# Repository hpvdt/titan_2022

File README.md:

# TITAN Video System

This is the code and hardware that is used to drive the electronics aboard TITAN for the "drive-by-video" system used for the World Human Powered Speed Challenge 2022.

>[!NOTE]
> This repository is meant to a snapshot of the system used for the 2022 system for TITAN, and was archived in November 2023. It was only unarchived to add a written summary of [operating instructions](./OPERATION.md) should it need to be reused. However no changes to the system itself have happened since 2023.
>
> For information on the the newest system in 2026 please go to that one's [separate repository](https://github.com/savob/titan_2026).

This code is spread across two types of devices, an STM32 microcontroller (STM32F103C8 is used in current models) and Raspberry Pis (RPi) Model 3B+'s. Each rider has an RPi for a total of two units, while there is only one STM32 for the vehicle. The STM32 is primarily responsible for collecting vehicle data and passing it to the RPis when requested. The RPis are responsible for displaying the video feed from the RPi Cameras used (hence why each rider needs their own) with an overlay of data collected inside the vehicle. This overlay is tailored to each rider.

There is an additional redundant video system for the front rider based on analog video to minimize potential failure points. This system was entirely off the shelf except for the power regulator, and was entirely disconnected from the remainder of TITAN's electronics to prevent any failure cascade affecting it.

## Folders

The repository is split into folders based on function.

Folder | Purpose
------ | -------
`Hardware` | Hardware files for our circuit boards
`Microcontroller Code` | STM32 Code
`vision` | RPi video code in C

## Hardware

The hardware for TITAN was all designed in [KiCad](https://www.kicad.org/) there are all three boards designed for TITAN with a `readme.md` explaining their purposes. Below is a block diagram of the TITAN system.

## Microcontroller Code

This is the collection of code prepared for the microcontroller on TITAN. It contains the unit tests we prepared when developing and testing different features that would eventually be integrated into TITAN, a local copy of the GPS library we use, and the overall program for TITAN.

TITAN was initially coded entirely within the Arduino IDE, however we migrated to using VS Code and PlatformIO to help make development easier and also make use of debugging features absent in the original Arduino IDE.

## Raspberry Pi Code

These are responsible for putting video on the displays for the riders to see, overlaid with information about TITAN. One of the RPi's has an ANT+ USB module used to collect data from the heart rate monitor and power pedals each rider has and feed it to the STM32 to pass onto the other RPi.

**The program for running the video feed is run as a separate process to the overlay**, this way if there is a hardware malfunction for the overlay (e.g. the STM32 freezes) then the video feed is uninterrupted for the riders.

The code for vision is split between Python and C. The video related code is written in Python, as well as a few other scripts for operation. The overlay code is written in C using the chipset driver library unique to the RPi 3 hardware to draw the overlay so it cannot be used on RPi models other then the 3B or 3B+ (and must be compiled specifically for each model).

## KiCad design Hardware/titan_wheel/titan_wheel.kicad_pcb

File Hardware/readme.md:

# TITAN Hardware

These folders contain the files related to hardware designed to operate TITAN. They were all designed using KiCad 6.0.2.

## Overview

The TITAN hardware is designed to primarily be a HAT (**HA**rdware on **T**op) for the Raspberry Pi 3B+s we use for video. This form factor was chosen to reduce the overall footprint of the system compared to the original 2019 system which used a ribbon cable between the RPi and boards. This also reduces the chance of incorrect connections since the HAT can only be seated one way. At the heart of the HAT, there is an STM32F103C microcontroller which communicates with the RPis and various sensors around TITAN via the various connections present.

These HATs perform 4 main functions:
1. Regulate power for their RPi and monitor from the battery. (Reverse polarity and undervoltage protection built in).
2. Facilitate communication between RPis via an STM32 microcontroller
3. Collect data from TITAN using the STM32 microcontroller
4. Handle telemetry with the chase vechicle

**Functions 2 to 4 are only performed on the "main" (front) unit, where the STM32 is.** The secondary (rear) does not have the STM32 mounted and just uses the power system and a header to connect to the main board for data.

## The Boards

There are three boards/folders/projects present in the folder, representing two revisions of the hardware. 

### TITAN Redux (2020)

Following feedback from the 2019 WHPSC and experience in developing [Blueshift](https://github.com/hpvdt/blueshift), an initial revision of TITAN was made in the fall of 2020, dubbed `titan_redux`. This was the main revision from the 2019 system, moving to the HAT form factor which worked on Blueshift as well as moving to embed the microconroller directly on the board (as opposed to seating a "Blue Pill" development board) and using SMT to reduce the overall size.

This was largely successful and allowed most of the code that went into TITAN in 2022 to be properly tested. There were only two notable issues with it:
1. The RX and TX lines for the GPS were not properly crossed over to the STM32.
2. The 5V regulator was removed for undocumented reasons, likely due to a failure.

### TITAN 2022

The more straightforwardly named `titan_2022` is a revision of the Redux board. It addresses the issues it had as well as adding support for new features while maintaining the same RPi HAT form. A brief of the changes:

- Fixed UART lines
- Rearranged board for improved button access
- Rearranged sensors to simplify routing
- Changed to a different 5V regulator (largely due to supply issues)
- Moved DHT sensor and encoder comparator off-board
- Added headers for monitoring CO2 and brake temperature

### TITAN Wheel (2022)

As part of the revision process from redux to the 2022 system a daughter board to collect wheel data was prepared called `titan_wheel`. This board houses the brake temperature sensor as well as the optical encoder and its conditioning circuitry. It was designed to fit within the wheel structure close to the brake disk.

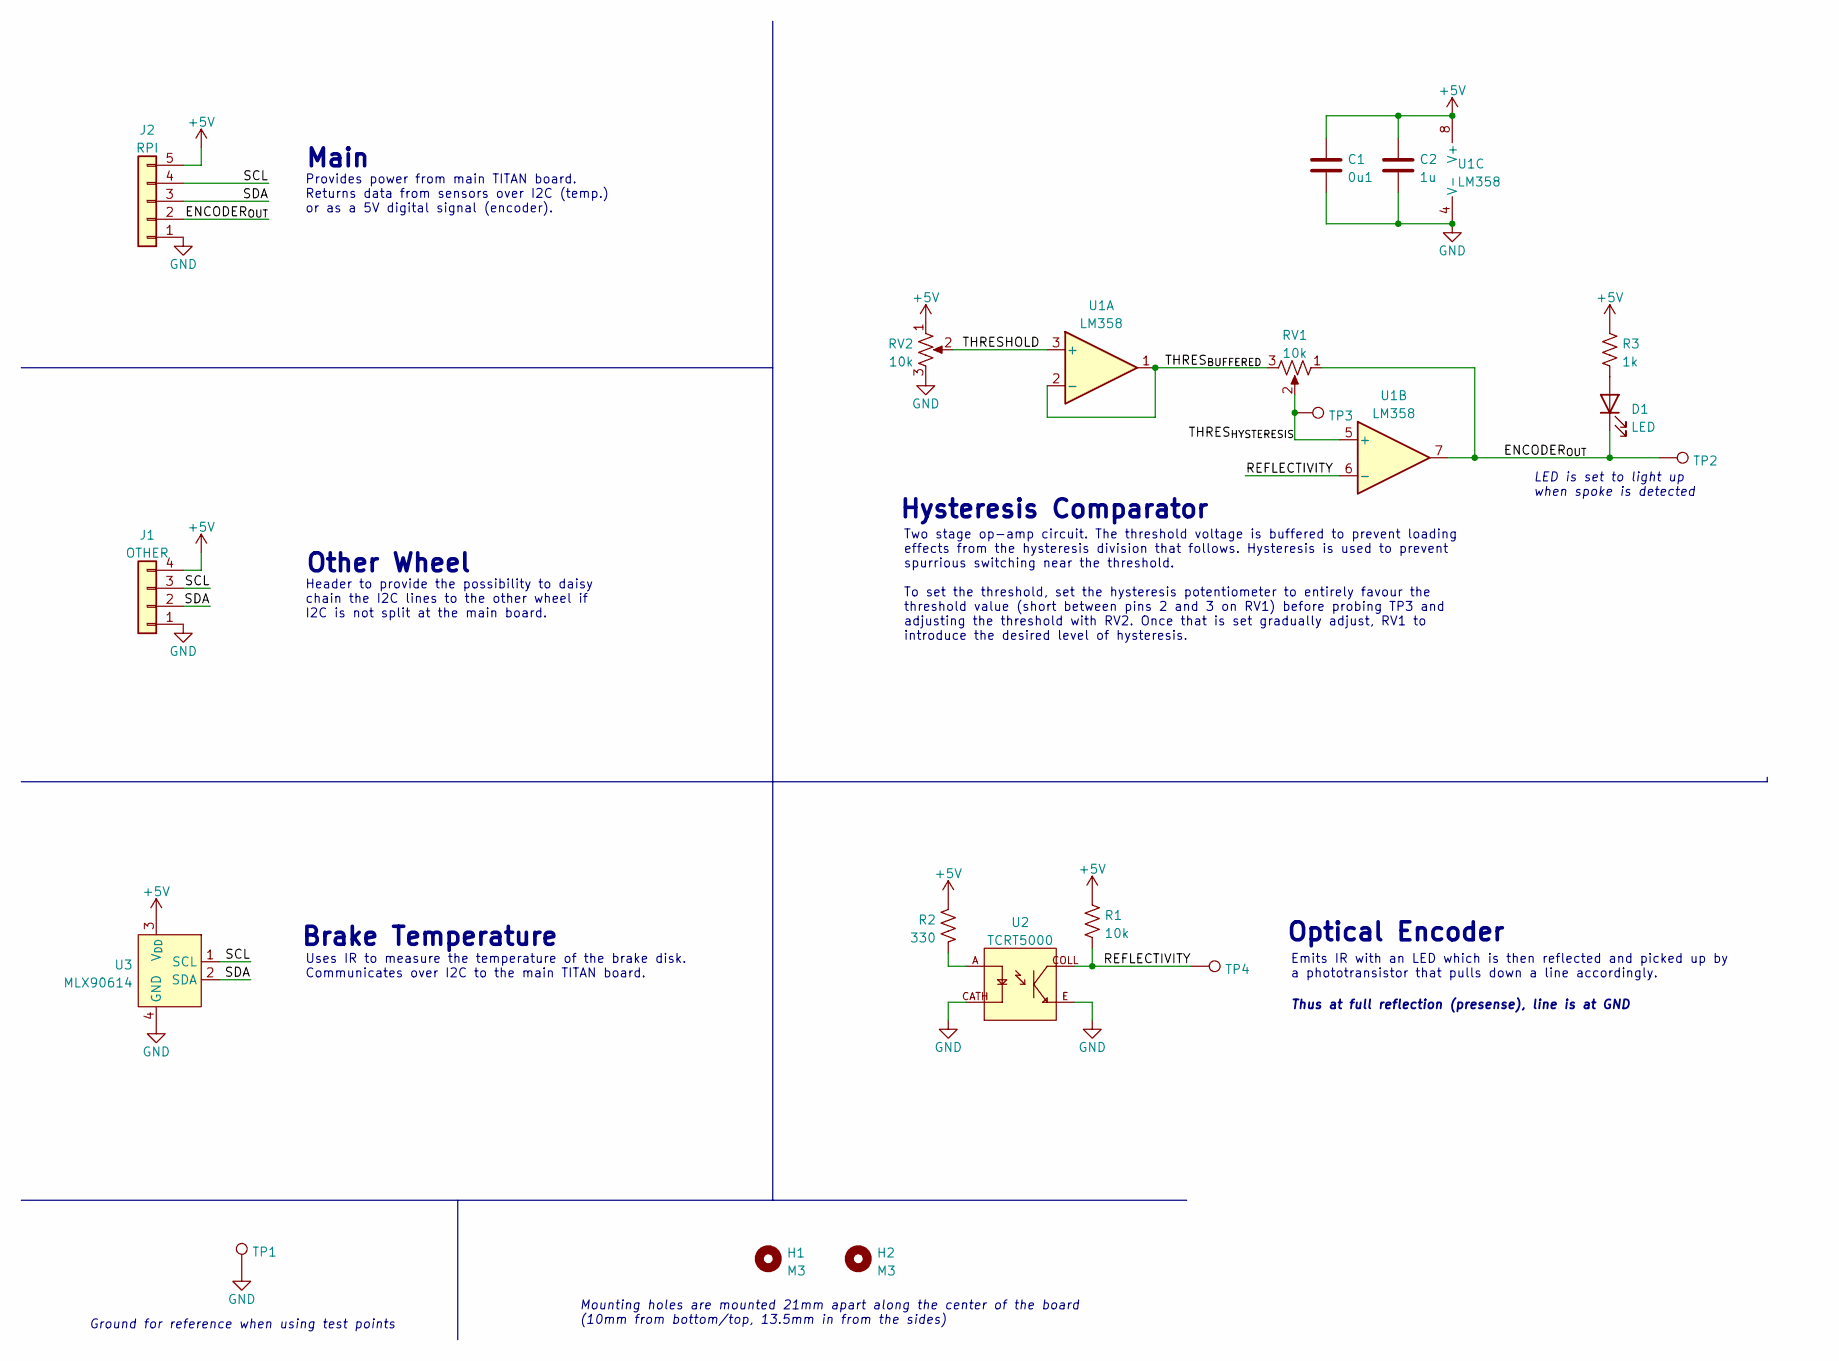
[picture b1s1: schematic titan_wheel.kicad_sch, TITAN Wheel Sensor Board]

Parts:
C1: 0u1; C_0603_1608Metric
C2: 1u; C_0603_1608Metric
D1: LED; LED_0805_2012Metric
H1, H2: M3; MountingHole_3.2mm_M3
J1: OTHER; PinHeader_1x04_P2.54mm_Vertical
J2: RPI; PinHeader_1x05_P2.54mm_Vertical
R1: 10k; R_0603_1608Metric
R2: 330; R_0603_1608Metric
R3: 1k; R_0603_1608Metric
RV1, RV2: 10k; Potentiometer_Vishay_T73YP_Vertical
TP1, TP2, TP3, TP4: TestPoint; TestPoint_Bridge_Pitch2.54mm_Drill1.0mm
U1: LM358; SOIC-8_3.9x4.9mm_P1.27mm
U2: TCRT5000; OPTO_TCRT5000; PARTREV 1.7
U3: MLX90614; TO-39-4_Window

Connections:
+5V: C1.1, C2.1, J1.4, J2.5, R1.1, R2.2, R3.1, RV2.1, U1.8 (V+), U3.3 (V_{DD})
/ENCODER_{OUT}: D1.1 (K), J2.2, RV1.1, TP2.1, U1.7
/REFLECTIVITY: R1.2, TP4.1, U1.6 (-), U2.COLL
/SCL: J1.3, J2.4, U3.1 (SCL)
/SDA: J1.2, J2.3, U3.2 (SDA)
/THRESHOLD: RV2.2, U1.3 (+)
/THRES_{BUFFERED}: RV1.3, U1.1, U1.2 (-)
/THRES_{HYSTERESIS}: RV1.2, TP3.1, U1.5 (+)
GND: C1.2, C2.2, J1.1, J2.1, RV2.3, TP1.1, U1.4 (V-), U2.CATH, U2.E, U3.4 (GND)
unnamed: D1.2 (A), R3.2
unnamed: R2.1, U2.A

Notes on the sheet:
Mounting holes are mounted 21mm apart along the center of the board (10mm from bottom/top, 13.5mm in from the sides)
Hysteresis Comparator
Provides power from main TITAN board. Returns data from sensors over I2C (temp.) or as a 5V digital signal (encoder).
Emits IR with an LED which is then reflected and picked up by a phototransistor that pulls down a line accordingly.
Two stage op-amp circuit. The threshold voltage is buffered to prevent loading effects from the hysteresis division that follows. Hysteresis is used to prevent spurrious switching near the threshold. To set the threshold, set the hysteresis potentiometer to entirely favour the threshold value (shor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
Ground for reference when using test points
Optical Encoder
Main
Other Wheel
LED is set to light up when spoke is detected
Brake Temperature
Header to provide the possibility to daisy chain the I2C lines to the other wheel if I2C is not split at the main board.
Uses IR to measure the temperature of the brake disk. Communicates over I2C to the main TITAN board.
Thus at full reflection (presense), line is at GND

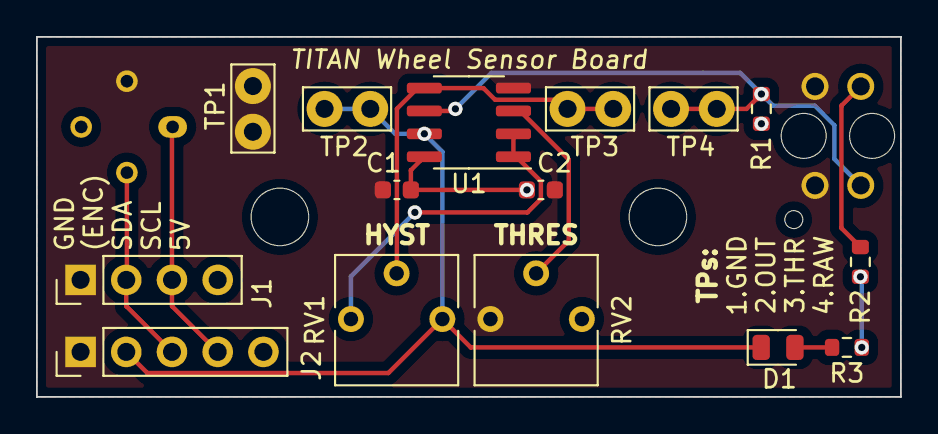
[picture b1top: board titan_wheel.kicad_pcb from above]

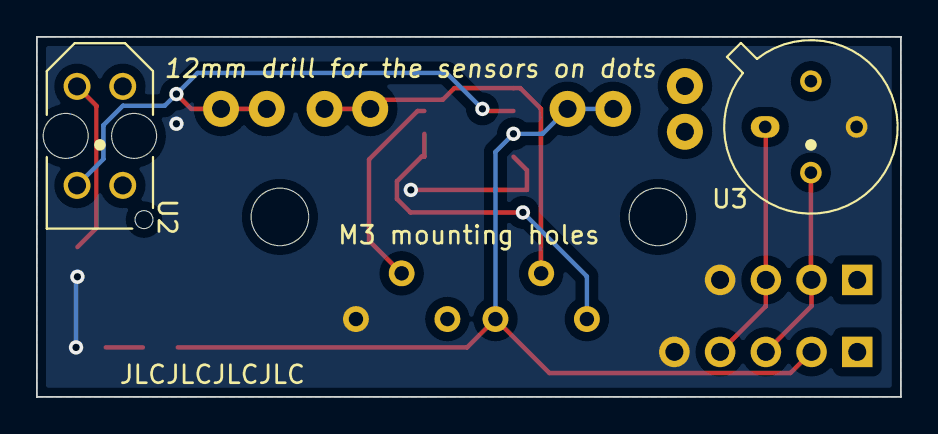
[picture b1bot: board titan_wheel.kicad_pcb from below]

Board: 2 copper layers, 48.0 x 20.0 mm, 19 parts (2 on the bottom side), 11 nets.

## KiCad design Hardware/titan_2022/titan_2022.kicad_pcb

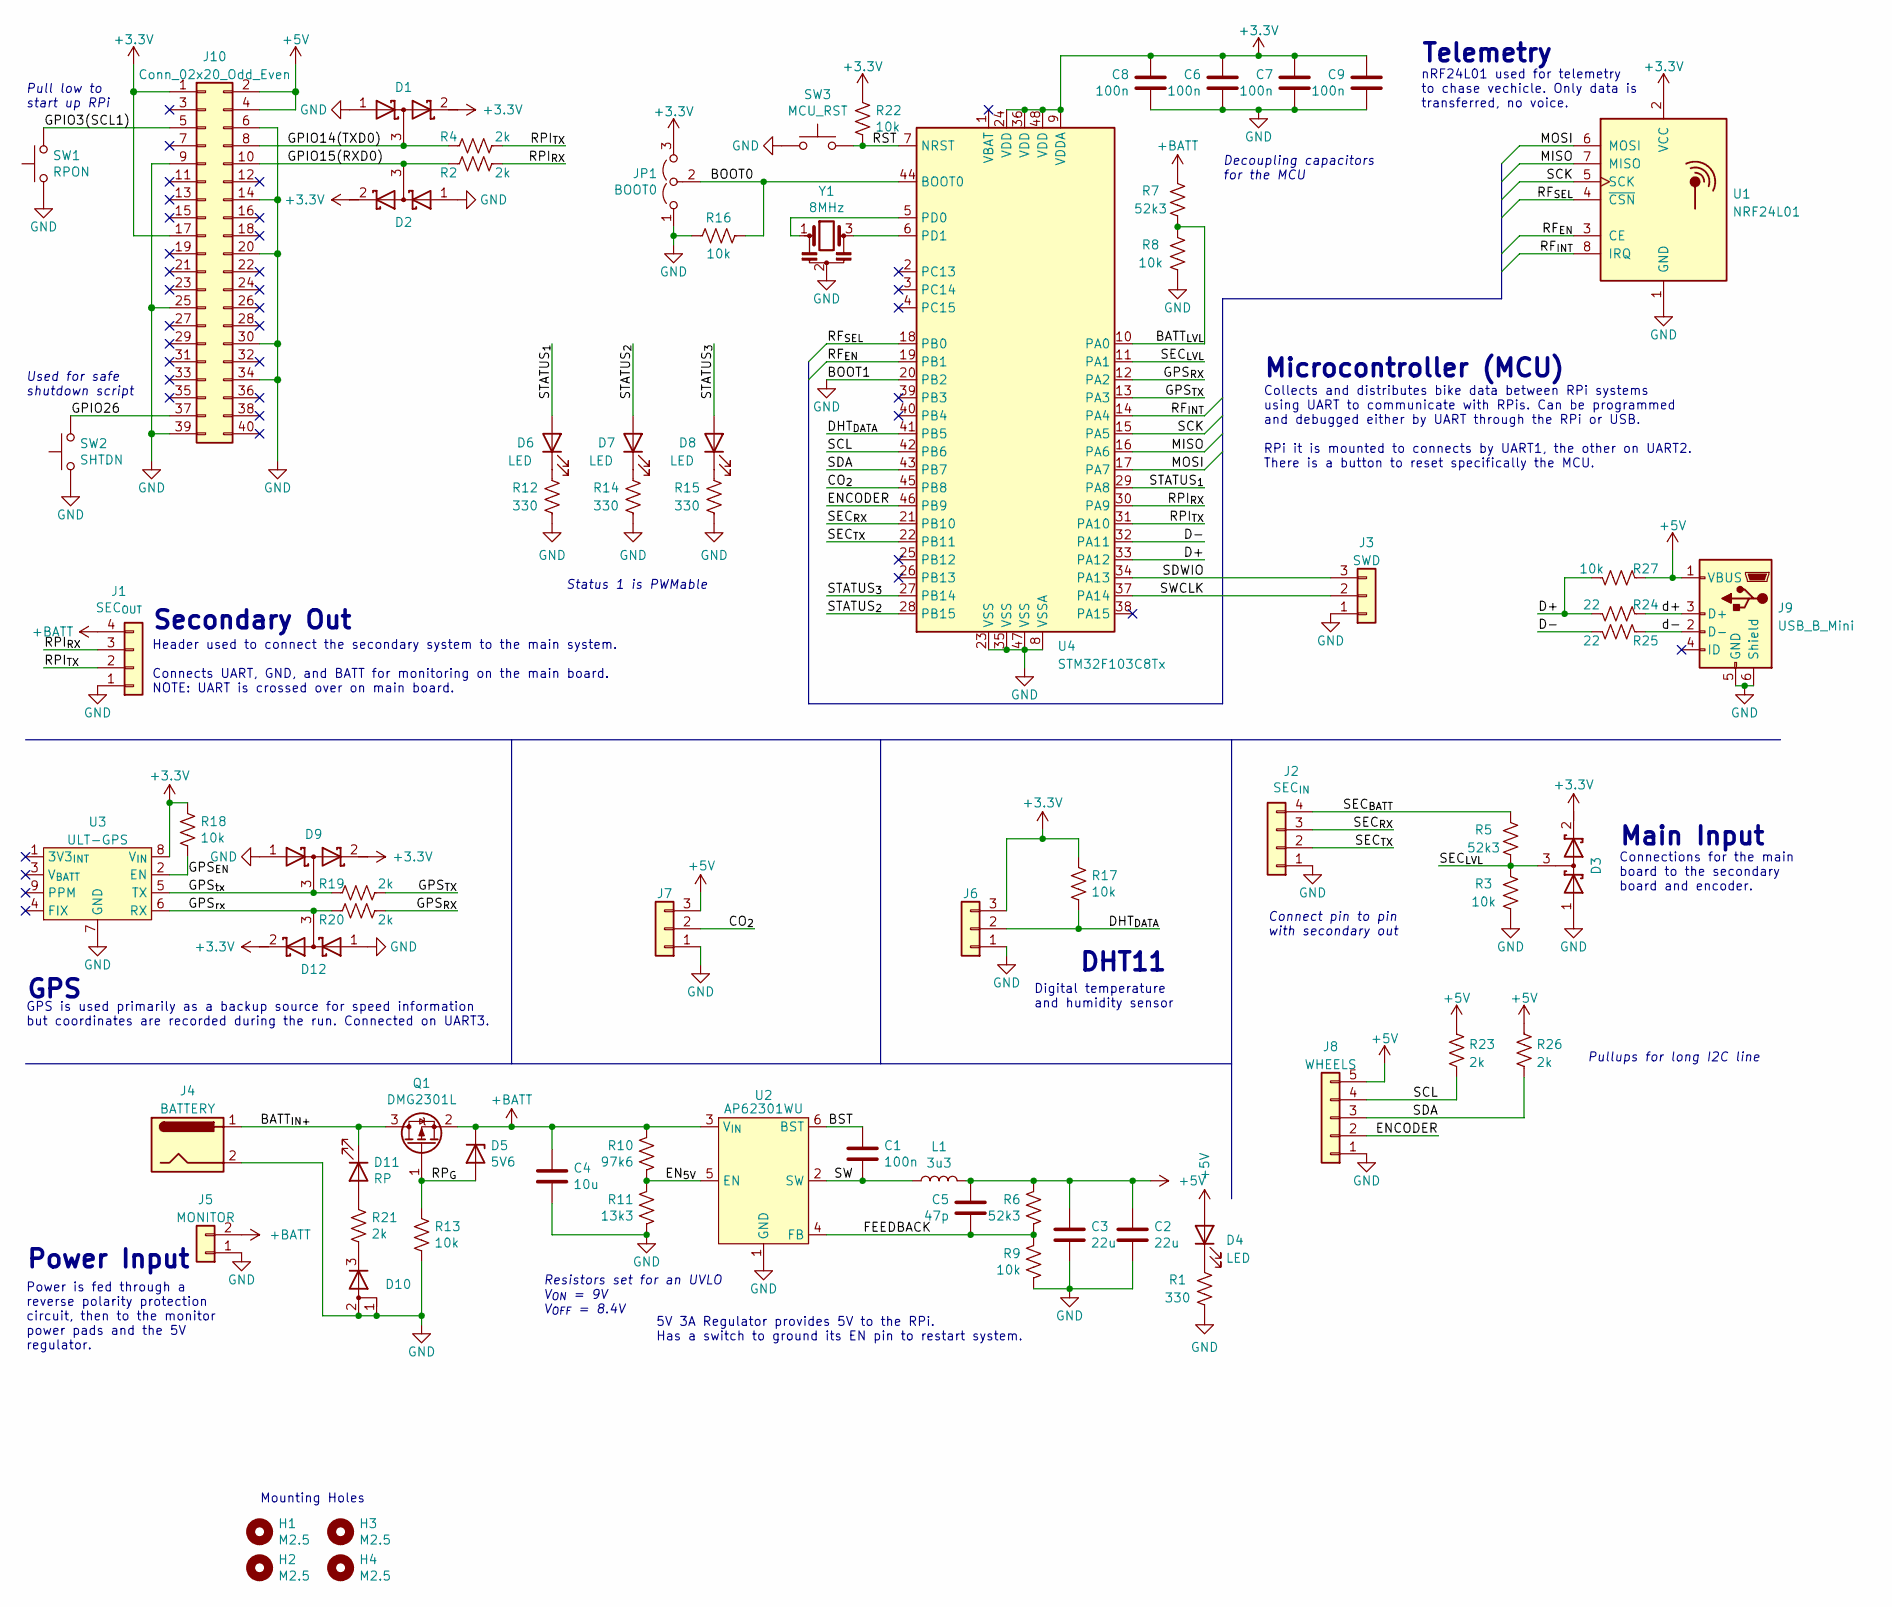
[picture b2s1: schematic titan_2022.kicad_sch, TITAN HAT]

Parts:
C1, C6, C7, C8, C9: 100n; C_0603_1608Metric
C2, C3: 22u; C_0805_2012Metric
C4: 10u; C_0603_1608Metric
C5: 47p; C_0603_1608Metric
D1, D2, D3, D9, D12: TBAT54S; SOT-23
D4, D6, D7, D8: LED; LED_0805_2012Metric
D5: 5V6; D_SOD-323
D10: BAV70; SOT-23
D11: RP; D_0805_2012Metric
H1, H2, H3, H4: M2.5; MountingHole_2.7mm_M2.5
J1: SEC_{OUT}; Molex_KK-254_AE-6410-04A_1x04_P2.54mm_Vertical
J2: SEC_{IN}; Molex_KK-254_AE-6410-04A_1x04_P2.54mm_Vertical
J3: SWD; PinHeader_1x03_P2.54mm_Vertical
J4: BATTERY; BarrelJack_Wuerth_6941xx301002
J5: MONITOR; SolderWire-1.5sqmm_1x02_P6mm_D1.7mm_OD3mm
J6: DHT; PinHeader_1x03_P2.54mm_Vertical
J7: CO_{2}; PinHeader_1x03_P2.54mm_Vertical
J8: WHEELS; PinHeader_1x05_P2.54mm_Vertical
J9: USB_B_Mini; TE_2172034-1
J10: Conn_02x20_Odd_Even; PinSocket_2x20_P2.54mm_Vertical
JP1: BOOT0; PinHeader_1x03_P2.54mm_Vertical
L1: 3u3; L_Taiyo-Yuden_NR-50xx
Q1: DMG2301L; SOT-23
R1, R12, R14, R15: 330; R_0603_1608Metric
R2, R4, R19, R20, R21, R23, R26: 2k; R_0603_1608Metric
R3, R8, R9, R13, R16, R17, R18, R22, R27: 10k; R_0603_1608Metric
R5, R6, R7: 52k3; R_0603_1608Metric
R10: 97k6; R_0603_1608Metric
R11: 13k3; R_0603_1608Metric
R24, R25: 22; R_0603_1608Metric
SW1: RPON; SW_PUSH_6mm_H4.3mm
SW2: SHTDN; SW_PUSH_6mm_H4.3mm
SW3: MCU_RST; SW_PUSH_6mm_H4.3mm
U1: NRF24L01; nRF24L01_Breakout
U2: AP62301WU; TSOT-23-6
U3: ULT-GPS
U4: STM32F103C8Tx; LQFP-48_7x7mm_P0.5mm
Y1: 8MHz; Resonator_SMD_Murata_CSTxExxV-3Pin_3.0x1.1mm

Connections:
+3V3: C6.2, C7.2, C8.2, C9.2, D1.2 (K), D2.2 (K), D3.2 (K), D9.2 (K), D12.2 (K), J6.3, J10.1, J10.17, JP1.3 (B), R17.2, R18.2, R22.2, U1.2 (VCC), U3.8 (V_{IN}), U4.9 (VDDA), U4.24 (VDD), U4.36 (VDD), U4.48 (VDD)
+5V: C2.1, C3.1, C5.2, D4.2 (A), J7.3, J8.5, J9.1 (VBUS), J10.2, J10.4, L1.2, R6.2, R23.1, R26.1, R27.2
+BATT: C4.2, D5.1 (K), J1.4, J5.2, Q1.2 (S), R7.2, R10.2, U2.3 (V_{IN})
/BATT_{IN+}: D11.1 (K), J4.1, Q1.3 (D)
/BATT_{LVL}: R7.1, R8.2, U4.10 (PA0)
/BOOT0: JP1.2 (C), R16.2, U4.44 (BOOT0)
/BST: C1.2, U2.6 (BST)
/CO_{2}: J7.2, U4.45 (PB8)
/D+: R24.1, R27.1, U4.33 (PA12)
/D-: R25.1, U4.32 (PA11)
/DHT_{DATA}: J6.2, R17.1, U4.41 (PB5)
/ENCODER: J8.2, U4.46 (PB9)
/EN_{5V}: R10.1, R11.2, U2.5 (EN)
/FEEDBACK: C5.1, R6.1, R9.2, U2.4 (FB)
/GPIO3(SCL1): J10.5, SW1.2
/GPIO14(TXD0): D1.3 (common), J10.8, R4.2
/GPIO15(RXD0): D2.3 (common), J10.10, R2.2
/GPIO26: J10.37, SW2.2
/GPS_{EN}: R18.1, U3.2 (EN)
/GPS_{RX}: R20.1, U4.12 (PA2)
/GPS_{TX}: R19.1, U4.13 (PA3)
/GPS_{rx}: D12.3 (common), R20.2, U3.6 (RX)
/GPS_{tx}: D9.3 (common), R19.2, U3.5 (TX)
/MISO: U1.7 (MISO), U4.16 (PA6)
/MOSI: U1.6 (MOSI), U4.17 (PA7)
/RF_{EN}: U1.3 (CE), U4.19 (PB1)
/RF_{INT}: U1.8 (IRQ), U4.14 (PA4)
/RF_{SEL}: U1.4 (~CSN), U4.18 (PB0)
/RPI_{RX}: J1.3, R2.1, U4.30 (PA9)
/RPI_{TX}: J1.2, R4.1, U4.31 (PA10)
/RP_{G}: D5.2 (A), Q1.1 (G), R13.2
/RST: R22.1, SW3.2, U4.7 (NRST)
/SCK: U1.5 (SCK), U4.15 (PA5)
/SCL: J8.4, R23.2, U4.42 (PB6)
/SDA: J8.3, R26.2, U4.43 (PB7)
/SDWIO: J3.3, U4.34 (PA13)
/SEC_{BATT}: J2.4, R5.2
/SEC_{LVL}: D3.3 (common), R3.2, R5.1, U4.11 (PA1)
/SEC_{RX}: J2.3, U4.21 (PB10)
/SEC_{TX}: J2.2, U4.22 (PB11)
/STATUS_{1}: D6.2 (A), U4.29 (PA8)
/STATUS_{2}: D7.2 (A), U4.28 (PB15)
/STATUS_{3}: D8.2 (A), U4.27 (PB14)
/SW: C1.1, L1.1, U2.2 (SW)
/SWCLK: J3.2, U4.37 (PA14)
/d+: J9.3 (D+), R24.2
/d-: J9.2 (D-), R25.2
GND: C2.2, C3.2, C4.1, C6.1, C7.1, C8.1, C9.1, D1.1 (A), D2.1 (A), D3.1 (A), D9.1 (A), D10.1 (A), D10.2 (A), D12.1 (A), J1.1, J2.1, J3.1, J4.2, J5.1, J6.1, J7.1, J8.1, J9.5 (GND), J9.6 (Shield), J10.6, J10.9, J10.14, J10.20, J10.25, J10.30, J10.34, J10.39, JP1.1 (A), R1.1, R3.1, R8.1, R9.1, R11.1, R12.1, R13.1, R14.1, R15.1, R16.1, SW1.1, SW2.1, SW3.1, U1.1 (GND), U2.1 (GND), U3.7 (GND), U4.8 (VSSA), U4.20 (PB2), U4.23 (VSS), U4.35 (VSS), U4.47 (VSS), Y1.2
unnamed: D4.1 (K), R1.2
unnamed: D6.1 (K), R12.2
unnamed: D7.1 (K), R14.2
unnamed: D8.1 (K), R15.2
unnamed: D10.3 (K), R21.1
unnamed: D11.2 (A), R21.2
unnamed: U4.5 (PD0), Y1.1
unnamed: U4.6 (PD1), Y1.3

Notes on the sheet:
Power is fed through a reverse polarity protection circuit, then to the monitor power pads and the 5V regulator.
Microcontroller (MCU)
Connections for the main board to the secondary board and encoder.
GPS
Connect pin to pin with secondary out
Status 1 is PWMable
nRF24L01 used for telemetry to chase vechicle. Only data is transferred, no voice.
Decoupling capacitors for the MCU
Power Input
Collects and distributes bike data between RPi systems using UART to communicate with RPis. Can be programmed and debugged either by UART through the RPi or USB. RPi it is mounted to connects by UART1, the other on UART2. There is a button to reset specifically the MCU.
Header used to connect the secondary system to the main system. Connects UART, GND, and BATT for monitoring on the main board. NOTE: UART is crossed over on main board.
Secondary Out
Mounting Holes
Pullups for long I2C line
Digital temperature and humidity sensor
GPS is used primarily as a backup source for speed information but coordinates are recorded during the run. Connected on UART3.
Pull low to start up RPi
Used for safe shutdown script
5V 3A Regulator provides 5V to the RPi. Has a switch to ground its EN pin to restart system.
DHT11
Resistors set for an UVLO V_{ON} = 9V V_{OFF} = 8.4V
Main Input
Telemetry

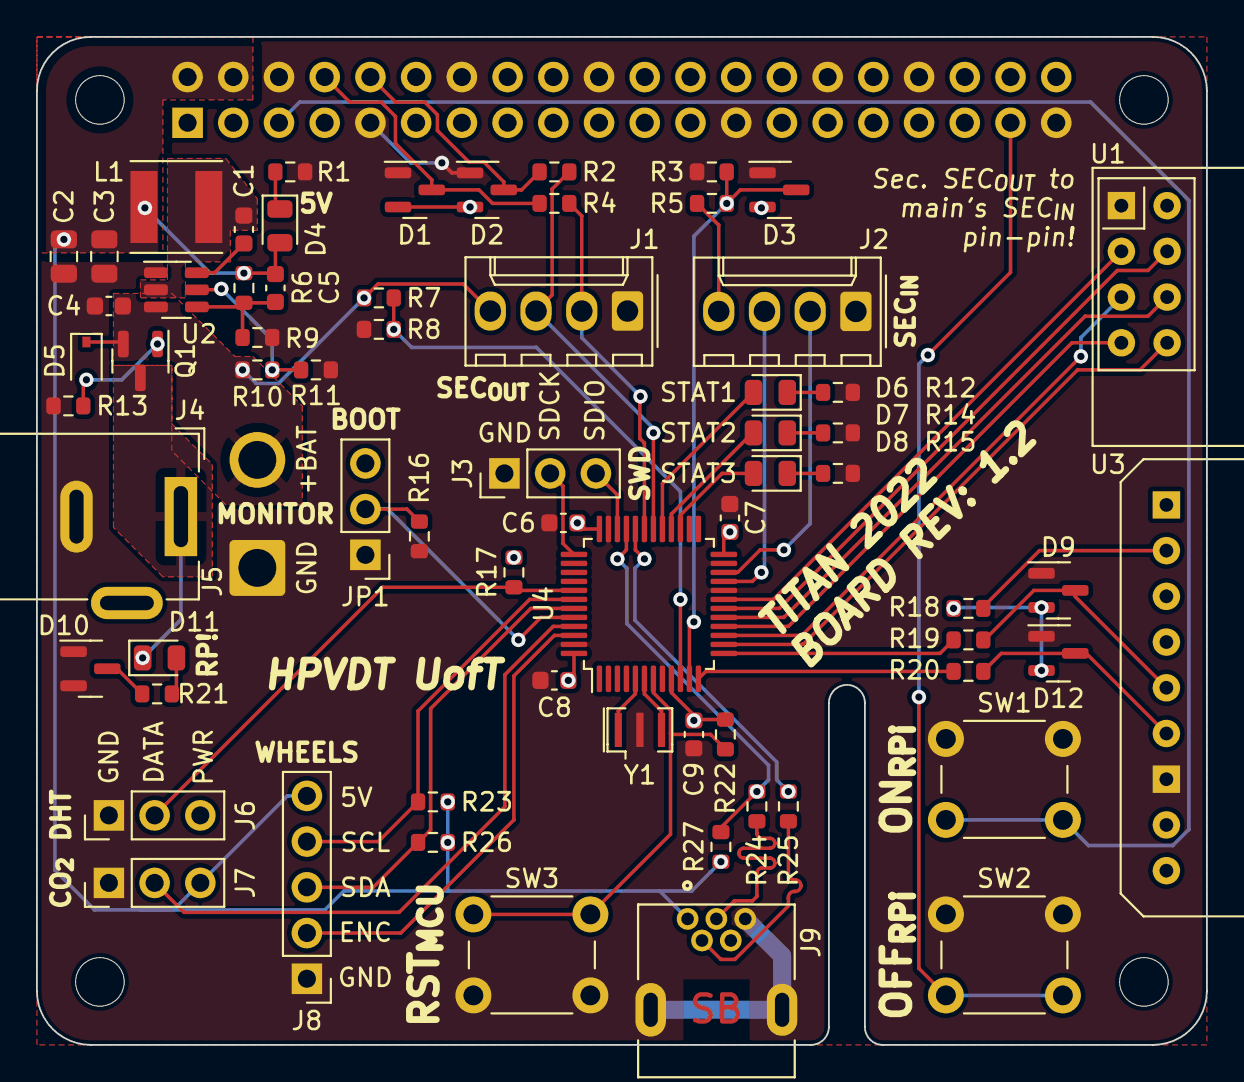
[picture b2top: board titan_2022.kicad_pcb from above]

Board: 2 copper layers, 65.0 x 56.0 mm, 73 parts (1 on the bottom side), 56 nets.

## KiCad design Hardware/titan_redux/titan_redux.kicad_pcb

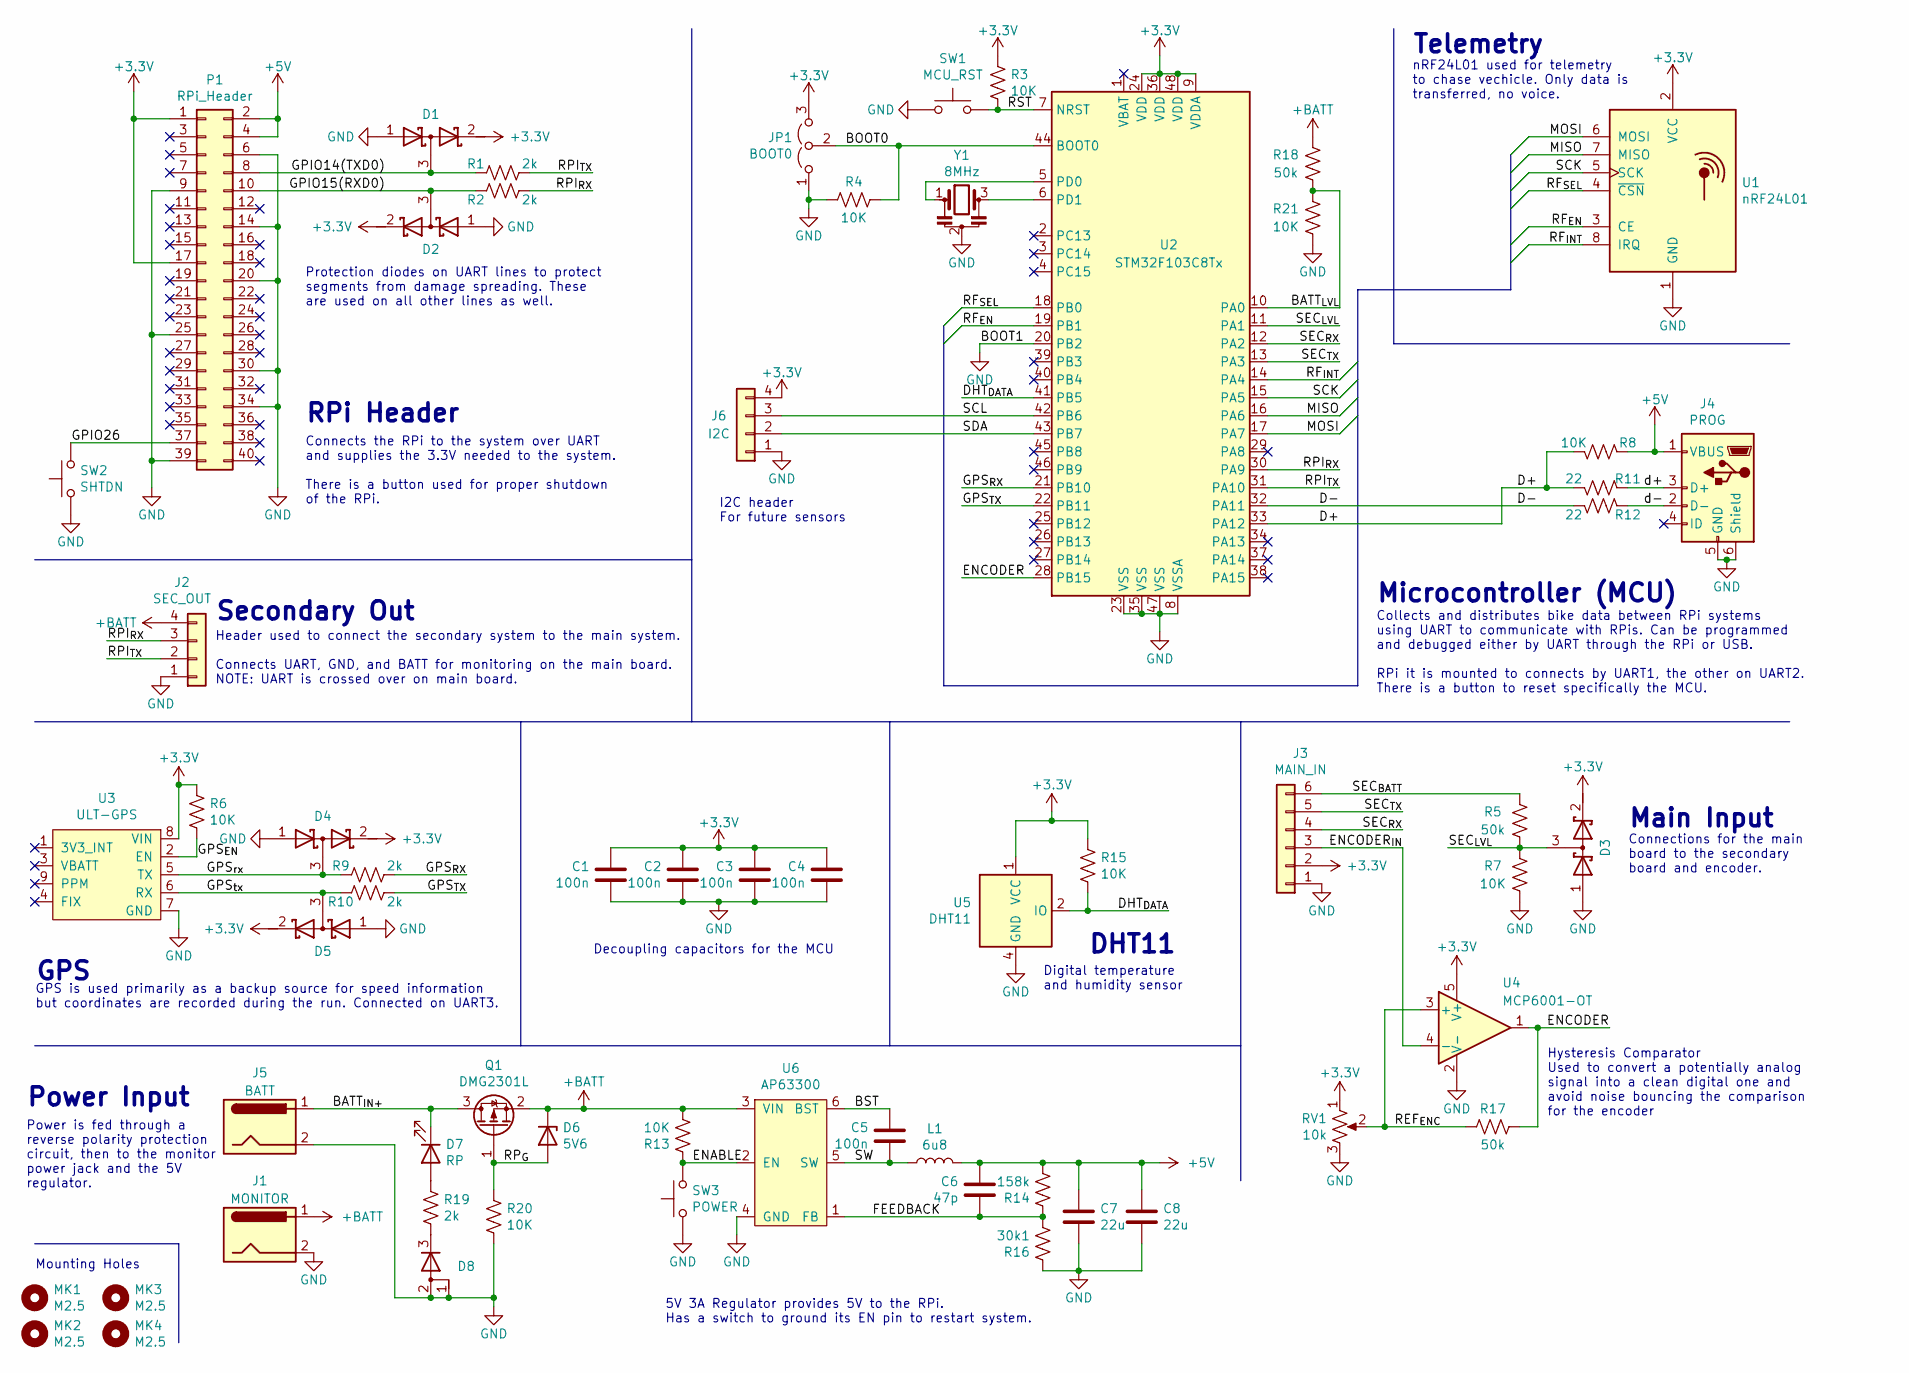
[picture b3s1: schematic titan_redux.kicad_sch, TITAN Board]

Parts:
C1, C2, C3, C4, C5: 100n; C_0603_1608Metric
C6: 47p; C_0603_1608Metric
C7, C8: 22u; C_0603_1608Metric
D1, D2, D3, D4, D5: TBAT54S; SOT-23
D6: 5V6; D_SOD-323
D7: RP; D_0805_2012Metric
D8: TCMBD914; SOT-23
J1: MONITOR; BarrelJack_Wuerth_6941xx301002
J2: SEC_OUT; PinHeader_1x04_P2.54mm_Vertical
J3: MAIN_IN; PinHeader_1x06_P2.54mm_Vertical
J4: PROG; TE_2172034-1
J5: BATT; BarrelJack_Wuerth_6941xx301002
J6: I2C; PinHeader_1x04_P2.54mm_Vertical
JP1: BOOT0; PinHeader_1x03_P2.54mm_Vertical
L1: 6u8; L_Bourns_SRN6045TA
MK1, MK2, MK3, MK4: M2.5; MountingHole_2.7mm_M2.5
P1: RPi_Header; PinSocket_2x20_P2.54mm_Vertical
Q1: DMG2301L; SOT-23
R1, R2, R9, R10, R19: 2k; R_0603_1608Metric
R3, R4, R6, R7, R8, R13, R15, R20, R21: 10K; R_0603_1608Metric
R5, R17, R18: 50k; R_0603_1608Metric
R11, R12: 22; R_0603_1608Metric
R14: 158k; R_0603_1608Metric
R16: 30k1; R_0603_1608Metric
RV1: 10k; Potentiometer_Bourns_3296W_Vertical
SW1: MCU_RST; SW_PUSH_6mm_H4.3mm
SW2: SHTDN; SW_PUSH_6mm_H4.3mm
SW3: POWER; SW_PUSH_6mm_H4.3mm
U1: nRF24L01; nRF24L01_Breakout
U2: STM32F103C8Tx; LQFP-48_7x7mm_P0.5mm
U3: ULT-GPS
U4: MCP6001-OT; SOT-23-5
U5: DHT11; Aosong_DHT11_5.5x12.0_P2.54mm
U6: AP63300; TSOT-23-6
Y1: 8MHz; Resonator_SMD_muRata_CSTxExxV-3Pin_3.0x1.1mm

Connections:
+3V3: C1.2, C2.2, C3.2, C4.2, D1.2 (K), D2.2 (K), D3.2 (K), D4.2 (K), D5.2 (K), J3.2, J6.4, JP1.3 (B), P1.1, P1.17, R3.2, R6.2, R15.2, RV1.1, U1.2 (VCC), U2.9 (VDDA), U2.24 (VDD), U2.36 (VDD), U2.48 (VDD), U3.8 (VIN), U4.5 (V+), U5.1 (VCC)
+5V: C6.2, C7.1, C8.1, J4.1 (VBUS), L1.2, P1.2, P1.4, R8.2, R14.1
+BATT: D6.1 (K), J1.1, J2.4, Q1.2 (S), R13.1, R18.2, U6.3 (VIN)
/BATT_{IN+}: D7.1 (K), J5.1, Q1.3 (D)
/BATT_{LVL}: R18.1, R21.2, U2.10 (PA0)
/BOOT0: JP1.2 (C), R4.2, U2.44 (BOOT0)
/BST: C5.2, U6.6 (BST)
/D+: R8.1, R11.1, U2.33 (PA12)
/D-: R12.1, U2.32 (PA11)
/DHT_{DATA}: R15.1, U2.41 (PB5), U5.2 (IO)
/ENABLE: R13.2, SW3.2, U6.2 (EN)
/ENCODER: R17.2, U2.28 (PB15), U4.1
/ENCODER_{IN}: J3.3, U4.4 (-)
/FEEDBACK: C6.1, R14.2, R16.1, U6.1 (FB)
/GPIO14(TXD0): D1.3 (common), P1.8, R1.2
/GPIO15(RXD0): D2.3 (common), P1.10, R2.2
/GPIO26: P1.37, SW2.2
/GPS_{EN}: R6.1, U3.2 (EN)
/GPS_{RX}: R9.1, U2.21 (PB10)
/GPS_{TX}: R10.1, U2.22 (PB11)
/GPS_{rx}: D4.3 (common), R9.2, U3.5 (TX)
/GPS_{tx}: D5.3 (common), R10.2, U3.6 (RX)
/MISO: U1.7 (MISO), U2.16 (PA6)
/MOSI: U1.6 (MOSI), U2.17 (PA7)
/REF_{ENC}: R17.1, RV1.2, U4.3 (+)
/RF_{EN}: U1.3 (CE), U2.19 (PB1)
/RF_{INT}: U1.8 (IRQ), U2.14 (PA4)
/RF_{SEL}: U1.4 (~CSN), U2.18 (PB0)
/RPI_{RX}: J2.3, R2.1, U2.30 (PA9)
/RPI_{TX}: J2.2, R1.1, U2.31 (PA10)
/RP_{G}: D6.2 (A), Q1.1 (G), R20.2
/RST: R3.1, SW1.2, U2.7 (NRST)
/SCK: U1.5 (SCK), U2.15 (PA5)
/SCL: J6.3, U2.42 (PB6)
/SDA: J6.2, U2.43 (PB7)
/SEC_{BATT}: J3.6, R5.2
/SEC_{LVL}: D3.3 (common), R5.1, R7.2, U2.11 (PA1)
/SEC_{RX}: J3.4, U2.12 (PA2)
/SEC_{TX}: J3.5, U2.13 (PA3)
/SW: C5.1, L1.1, U6.5 (SW)
/d+: J4.3 (D+), R11.2
/d-: J4.2 (D-), R12.2
GND: C1.1, C2.1, C3.1, C4.1, C7.2, C8.2, D1.1 (A), D2.1 (A), D3.1 (A), D4.1 (A), D5.1 (A), D8.1 (A), D8.2 (A), J1.2, J2.1, J3.1, J4.5 (GND), J4.6 (Shield), J5.2, J6.1, JP1.1 (A), P1.6, P1.9, P1.14, P1.20, P1.25, P1.30, P1.34, P1.39, R4.1, R7.1, R16.2, R20.1, R21.1, RV1.3, SW1.1, SW2.1, SW3.1, U1.1 (GND), U2.8 (VSSA), U2.20 (PB2), U2.23 (VSS), U2.35 (VSS), U2.47 (VSS), U3.7 (GND), U4.2 (V-), U5.4 (GND), U6.4 (GND), Y1.2
unnamed: D7.2 (A), R19.2
unnamed: D8.3 (K), R19.1
unnamed: U2.5 (PD0), Y1.1
unnamed: U2.6 (PD1), Y1.3

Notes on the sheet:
5V 3A Regulator provides 5V to the RPi. Has a switch to ground its EN pin to restart system.
Connections for the main board to the secondary board and encoder.
DHT11
Power Input
Telemetry
Main Input
Mounting Holes
GPS is used primarily as a backup source for speed information but coordinates are recorded during the run. Connected on UART3.
nRF24L01 used for telemetry to chase vechicle. Only data is transferred, no voice.
Connects the RPi to the system over UART and supplies the 3.3V needed to the system. There is a button used for proper shutdown of the RPi.
Collects and distributes bike data between RPi systems using UART to communicate with RPis. Can be programmed and debugged either by UART through the RPi or USB. RPi it is mounted to connects by UART1, the other on UART2. There is a button to reset specifically the MCU.
Protection diodes on UART lines to protect segments from damage spreading. These are used on all other lines as well.
GPS
I2C header For future sensors
Digital temperature and humidity sensor
RPi Header
Power is fed through a reverse polarity protection circuit, then to the monitor power jack and the 5V regulator.
Header used to connect the secondary system to the main system. Connects UART, GND, and BATT for monitoring on the main board. NOTE: UART is crossed over on main board.
Decoupling capacitors for the MCU
Hysteresis Comparator Used to convert a potentially analog signal into a clean digital one and avoid noise bouncing the comparison for the encoder
Secondary Out
Microcontroller (MCU)

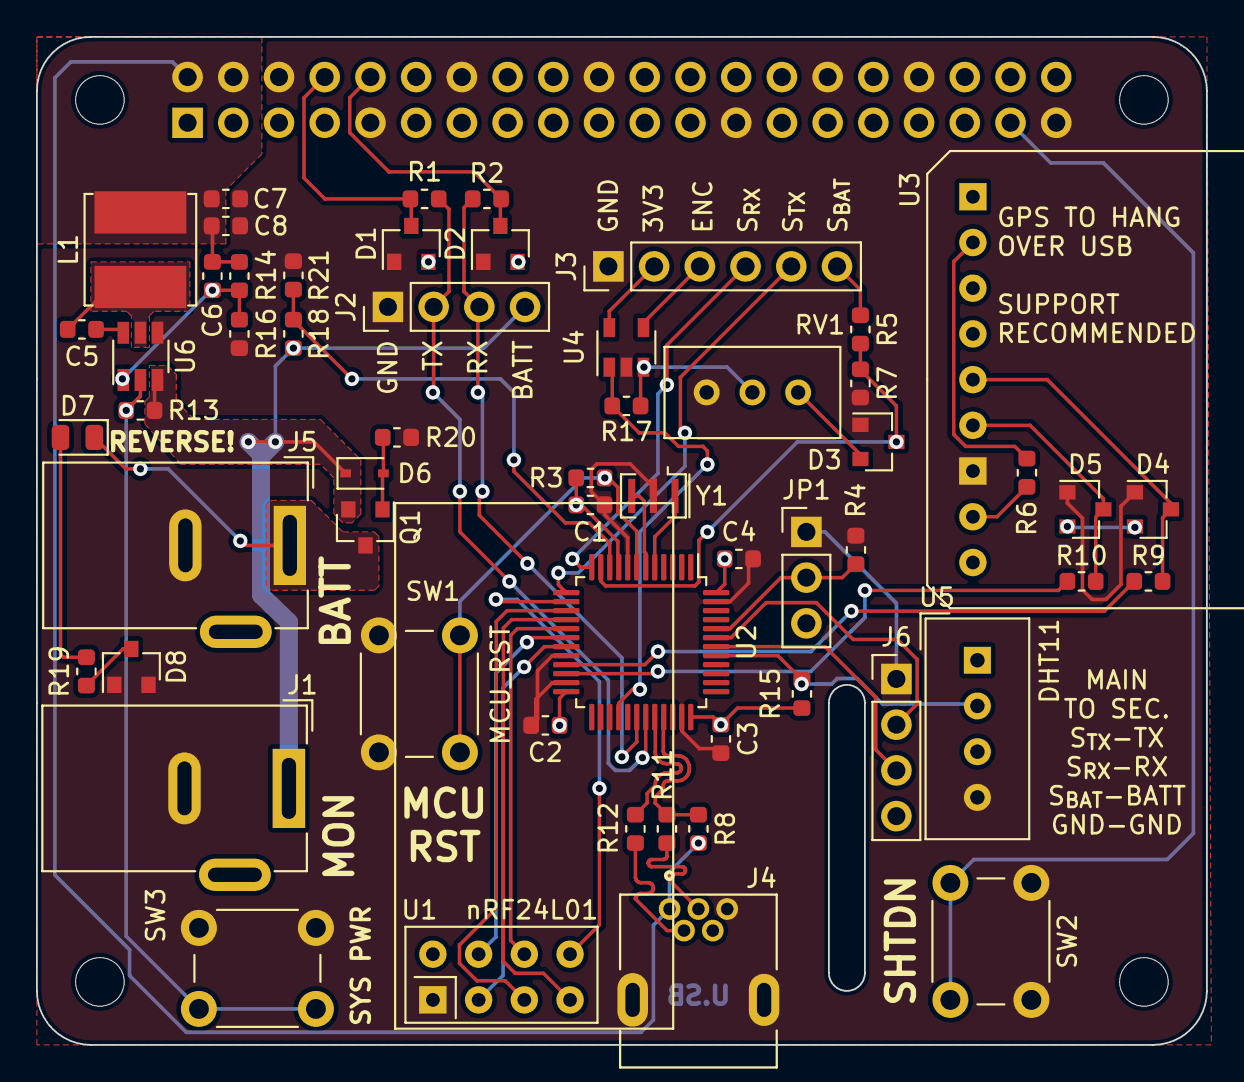
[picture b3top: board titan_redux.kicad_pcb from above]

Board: 2 copper layers, 65.0 x 56.0 mm, 62 parts (1 on the bottom side), 47 nets.

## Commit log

2019-11-03 Arduino code
    Initial commit
2019-11-03 Python Code
2019-11-03 Modified Python ANT+ Library
2019-11-04 Repiping errors
    - Changed OSD to use 'update' instead of layer swapping
    - Added code to output errors to a null device for the duration of 'update' to allow it to be run in terminal.
    - Cycle time cut down to ~70ms!
2019-11-07 Initiation of C++ version
    Started the C++ version folder for future use.
2019-12-24 C++ initial commit
2020-01-30 Fixing overlay
    Previous commit had a line commented out that was responsible for adding the overlay. Oops.
2020-02-07 Fixing font issues
    Made the font reference relative, not absolute to avoid issues if the folder name changes for the folder containing res and src
2021-02-20 Updated readme to be more informative
2021-06-07 Added python unit tests
2021-06-07 Added harware design files
2021-06-07 Added all microcontroller code
2021-06-07 Deleted redundant folder
2022-07-21 Delete TitanVisionFirmwarePython directory
    Not needed, moving to C-based OSD system
2022-07-21 Delete titan_vision_c++ directory
    Not using this c++ code
2022-07-21 Uploaded test files for openant
2022-07-21 Upload of C based OSD
    OSD based on writing directly to the video driver
2022-07-22 Initial working version with ANT
    Made a version that receives and shows the ANT data piped into the process (from the python ANT scripts)
2022-07-22 Delete titanant.py
    Moved to directory with other OSD code
2022-07-22 Marking out the need to update readme
2022-07-22 Added code to start and stop camera preview
2022-07-23 Updated Serial object definition
    Updated Serial object declaration to be in line with new STM32 core
    https://github.com/stm32duino/wiki/wiki/API#hardwareserial
2022-07-23 Chenged Serial object names
2022-07-23 Removed spare system code
2022-07-23 Removed LED code
2022-07-24 Made python script ignore temporary pipe issues
2022-07-24 Improved debug messaging for serial communication
2022-07-24 Matching STM32 specified baudrate
2022-07-24 Added system to disable camera for tests
2022-07-24 Moved variables into .c file forbetter scoping
2022-07-25 Migrated ANT code to seperate files
2022-07-25 Tidied up startup messages
2022-07-25 Redid check for serial line ANT
2022-07-25 Moved debug define into .c file
2022-07-25 Changed up ANT debug messages
2022-07-25 Redid timing related code
2022-07-25 Changed NULL to character constant
2022-07-25 Fixed string termination
2022-07-25 Added new time trial file for ease of use in other files
2022-07-25 Added serialTest file
2022-07-25 Added ability to batch send ANT data
2022-07-25 Setting stdin to non-blocking
2022-07-25 Added logging capabilities
2022-07-25 Added file for log directory
2022-07-25 Updated makefile to include new files
2022-07-27 Ported racesim to C
2022-07-27 Added comments for clarity
2022-08-02 Moving C log files into correct folder
2022-08-02 USB debugging to be toggled by build settings
2022-08-03 Added telemetry functionality
2022-08-03 Added Arduino based telemetry station code
2022-08-03 Added check for presence of a radio
2022-08-04 Added radio check to station code
2022-08-04 Fixed variable change
2022-08-04 Updated GPS code
2022-08-04 Removed comment for serial pins
2022-08-04 Fixed integer division for GPS distance
2022-08-04 Removed irrelevant encoder test code
2022-08-04 Added hardware timer test code
2022-08-04 Removed useless SPI related code
2022-08-15 Removing hardware files from 2019
2022-08-15 Upload of my 2020 redux hardware
2022-08-15 Uploaded TITAN 2022 electronics system as ordered
2022-08-15 Created hardware readme
2022-08-16 Cleaned up schematics
2022-08-17 Added scripts to start system and safely power down
2022-08-17 Allow program to be altered using arguements when called
2022-08-17 Accomodating new data from bike
2022-08-17 Began seperate overlays for riders
2022-08-18 Condensed arguement calls
2022-08-18 Fixing arguement parsing indexes
2022-08-18 Cleaned up ANT data handling
2022-08-18 Tuned overlay layouts for riders
2022-08-18 All log files/videos are indexed by file count in their names
2022-08-18 Updated start script to have right arguements for bike.bin
2022-08-19 Incorperating RaceSim
2022-08-19 Changed radio message variable name
2022-08-19 Added brake temperature
2022-08-19 Added CO2 sensor support
2022-08-19 Disabled radio prints
2022-08-19 Minor touches
2022-08-19 Added note for new data
2022-08-19 Moved some debug related stuff inside '#ifdef'
2022-08-19 Upload of inital PlatformIO based firmware
2022-08-19 Moved brake code to seperate files
2022-08-19 Moved telemetry, condensed main loop
2022-08-19 Added LED library
2022-08-19 Added hardware timer based encoder
2022-08-23 Fixed note for wheel LED
2022-08-23 Added build option for clone STM32s
2022-08-23 Removed redundant debug message
2022-08-23 Added checks for if a brake is missing or not
2022-08-23 Fixed heartbeat and added LED flashes in setup
2022-08-28 Fixed reading for rear brake temperature
2022-08-28 Added debug configuration
2022-08-30 Calibrated battery voltage division
2022-09-01 Added colour to C code print statements
2022-09-01 Explicitly make it run forever when numFrames is -1
2022-09-01 Matched serial lines with hardware
2022-09-01 Fixed original encoder code
2022-09-01 Tweaked battery system based on tests
2022-09-01 Make GPS distance a float division
2022-09-01 Hardcoded emissivity for brake disks
2022-09-06 Add GPS spd to display. Change power to avg power.
2022-09-07 divided circumference value by 1000
2022-09-07 modified files to work on raspberry pi
2022-09-07 Added ledSet and comments
2022-09-07 Added polling for CO2 sensor
2022-09-07 Interrupt based CO2 sensor monitoring
2022-09-07 Added blinking to brakes for error pick up
2022-09-07 Touching up some headers
2022-09-07 Added passthrough code for TITAN redux board
2022-09-12 Made one unified radio passthrough sketch
2022-09-12 Removed obsolete and outdated Arduino sketch for TITAN
2022-09-12 Fixed CO2 reading
2022-09-12 Implemented bilk data system for telemetry
2022-09-12 Added error LEDs to setups
2022-09-12 Set default radio power to maximum
2022-09-13 Changed name for encoder speed
2022-09-14 Generalized bulk transfer for RPis too
2022-09-14 Changed speed variable names for clarity and logging GPS distance
2022-09-15 Fixed power averaging issue
2022-09-15 Fixed return to desktop script
2022-09-15 Properly named ANT files
2022-09-15 Changed periodic power averaging to continuous averaging
2022-09-16 Added .gitignore
2022-10-02 Added/changed readmes
2022-12-31 Raised radio power to MAX
    Explains the short range of TITAN at WHPSC 2022. This should be tested for stability due to power draw, low if needed.
2023-01-16 Uploading block diagram file
2023-03-08 Updated readme with block diagram
2023-11-08 Update platformio.ini
    Made debugging server interpolated based on user install
2026-05-04 Added operation guide
2026-05-04 Spelling mistake
